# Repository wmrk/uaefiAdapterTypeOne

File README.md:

## License

Licensed under the [CERN Open Hardware Licence Version 2 - Strongly Reciprocal](LICENSE)
(`CERN-OHL-S-2.0`). The text in `LICENSE` is the unmodified canonical licence.

### Additional terms

The following terms are not part of CERN-OHL-S-2.0 and are stated here by the author:

- **#1:** This adapter is intended for off-road land and water vehicles.
- **#2:** This adapter is not compliant with automotive environmental regulations.
- **#3:** This adapter is not approved for manned aircraft applications.

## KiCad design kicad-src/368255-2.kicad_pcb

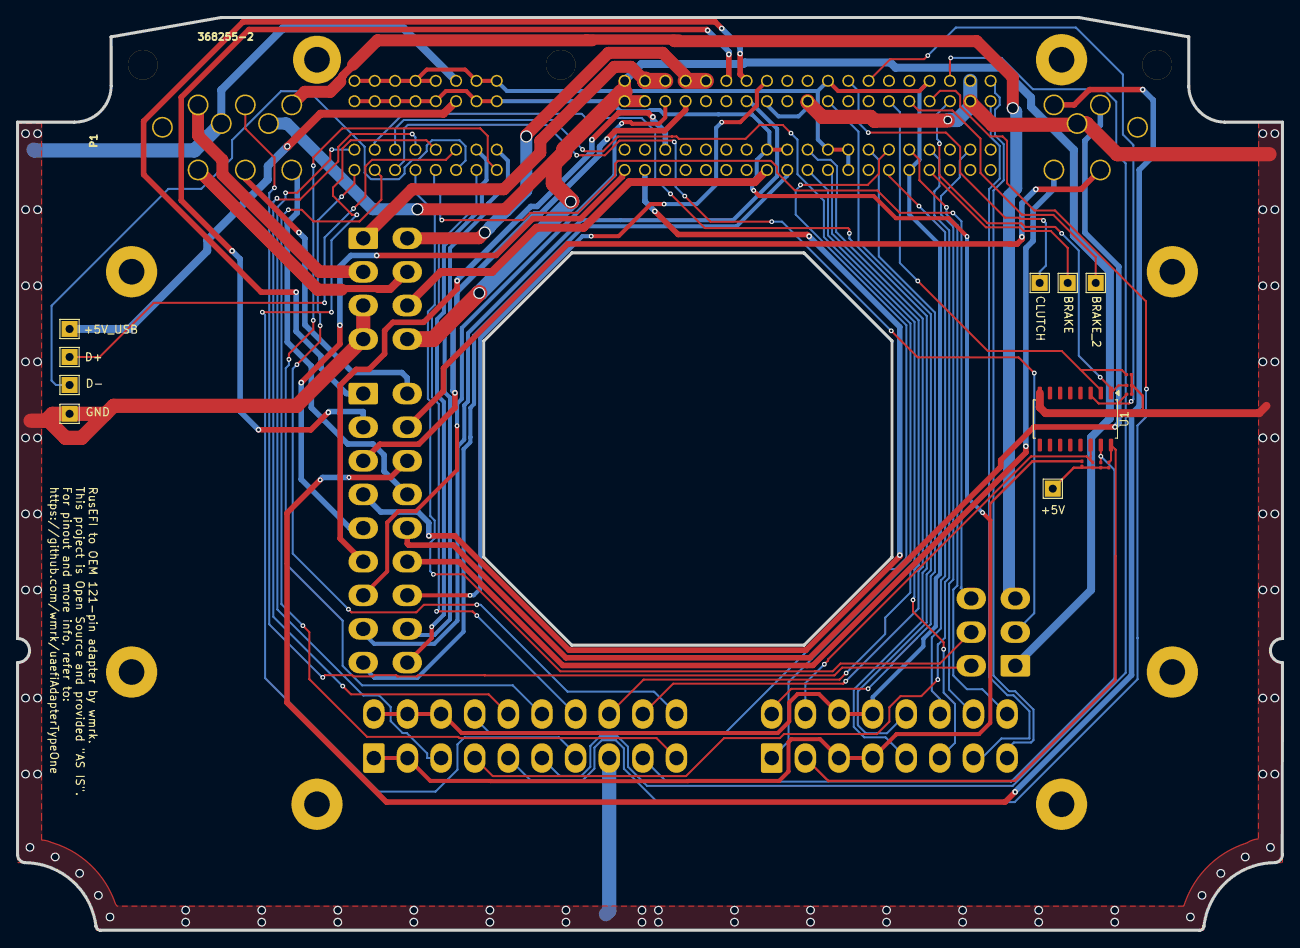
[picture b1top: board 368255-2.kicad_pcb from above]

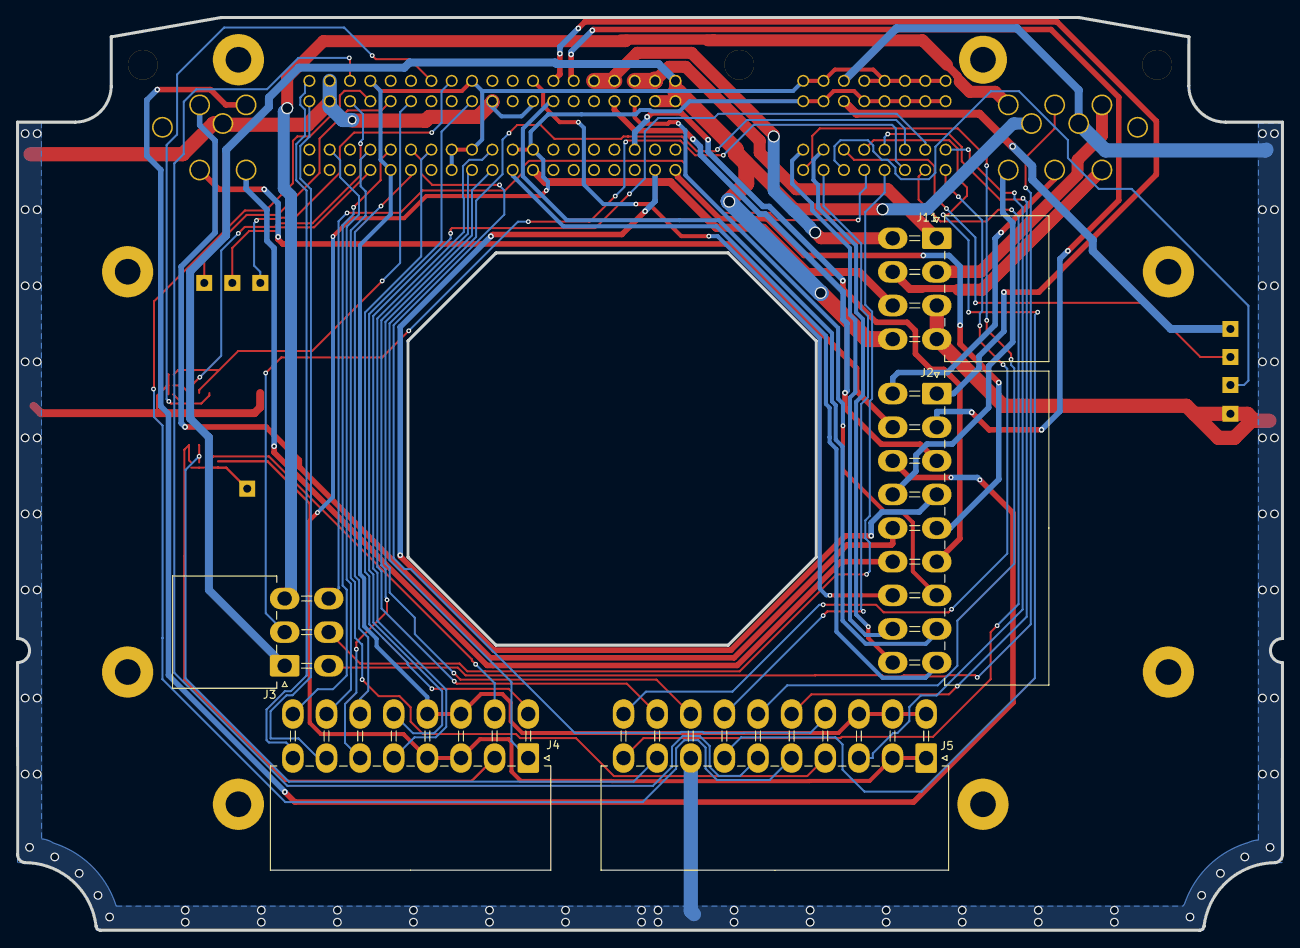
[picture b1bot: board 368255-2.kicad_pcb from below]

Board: 2 copper layers, 158.0 x 114.0 mm, 30 parts (12 on the bottom side), 68 nets.

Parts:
J2: 5569-18A2; Molex_Mini-Fit_Jr_5569-18A2_2x09_P4.20mm_Horizontal
J3: 5569-06A2; Molex_Mini-Fit_Jr_5569-06A2_2x03_P4.20mm_Horizontal
J4: 5569-16A2; Molex_Mini-Fit_Jr_5569-16A2_2x08_P4.20mm_Horizontal
J5: 5569-20A2-new; Molex_Mini-Fit_Jr_5569-20A2_2x10_P4.20mm_Horizontal
J11: 5569-08A2; Molex_Mini-Fit_Jr_5569-08A2_2x04_P4.20mm_Horizontal
J21, J22, J23, J24, J25, J26, J27, J28: Conn_01x01_Pin; TestPoint_THTPad_2.0x2.0mm_Drill1.0mm
P1: 368255-2
R1: R0; R_0201_0603Metric
R2, R3, R4, R8, R9, R10: 10k; R_0201_0603Metric
U1: ULN2003A; SOIC-16_4.55x10.3mm_P1.27mm
hole1: hole1; uaefi_hole
hole2: hole2; uaefi_hole
hole3: hole3; uaefi_hole
hole4: hole4; uaefi_hole
hole5: hole5; uaefi_hole
hole6: hole6; uaefi_hole
hole7: hole7; uaefi_hole
hole8: hole8; uaefi_hole

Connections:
+5VP: J4.3, J4.4, J5.1, J5.2, P1.32, P1.33, P1.90, P1.91, P1.93, P1.94, P1.95, P1.96, P1.97, R1.1
+5VUSB: J24.1 (Pin_1_1), P1.92
+12V: J3.1, J11.8, P1.44, P1.45, P1.63, P1.117
/1_WBO_Ip: J3.5, P1.110
/2_WBO_Vm: J3.6, P1.109
/3_WBO_Heater: J3.3, P1.114
/5_WBO_Rtrim: J3.2, P1.111
/6_WBO_Un: J3.4, P1.115
/12V_KEY_VIGN: J11.7, P1.13
/BRAKE_PEDAL_SENSOR: J22.1 (Pin_1_1), P1.21
/BRAKE_PEDAL_SENSOR_2: J23.1 (Pin_1_1), P1.58
/BUTTON1: P1.60, R10.2, U1.1 (I1)
/BUTTON3: P1.57, R9.2, U1.2 (I2)
/CAN+: J4.7, P1.62
/CAN-: J4.8, P1.81
/CLUTCH_SENSOR: J21.1 (Pin_1_1), P1.74
/CONTITIONER_ON: P1.75, R8.2, U1.3 (I3)
/EGT+: J5.10, P1.112
/EGT-: J5.20, P1.113
/IN_AUX1_EWG_POS_SENSOR: J4.1, P1.103
/IN_AUX2_WBO_ANALOG: J5.3, P1.105
/IN_AUX3_FUEL_PRESSURE_SENSOR: J5.15, P1.102
/IN_BUTTON1: J4.2, R2.2, U1.16 (O1)
/IN_BUTTON2: J4.10, R4.2, U1.14 (O3)
/IN_BUTTON3: J5.9, R3.2, U1.15 (O2)
/IN_CLT: J4.16, P1.39
/IN_FLEX: J4.5, P1.104
/IN_HALL1_SPEED_SENSOR: J5.5, P1.59
/IN_HALL2: J5.6, P1.79
/IN_HALL3: J5.7, P1.101
/IN_IAT: J4.15, P1.42
/IN_KNOCK_RAW: J4.14, P1.19
/IN_MAP: J4.9, P1.37
/IN_PPS1: J4.6, P1.16
/IN_PPS2: J5.4, P1.40
/IN_TPS1: J4.13, P1.54
/IN_TPS2: J5.14, P1.38
/OUT_DC1+: J11.5, P1.66, P1.67
/OUT_DC1-: J11.1, P1.64, P1.65
/OUT_DC2+: J11.6, P1.121
/OUT_DC2-: J11.2, P1.116
/OUT_IGN1: J2.15, P1.5
/OUT_IGN2: J2.14, P1.1
/OUT_IGN3: J2.12, P1.2
/OUT_IGN4: J2.11, P1.4
/OUT_IGN5: J2.13, P1.119
/OUT_IGN6: J2.10, P1.120
/OUT_INJ1: J2.6, P1.27
/OUT_INJ2: J2.5, P1.6
/OUT_INJ3: J2.4, P1.7
/OUT_INJ4: J2.3, P1.47
/OUT_INJ5: J2.2, P1.68
/OUT_INJ6: J2.1, P1.69
/OUT_LS1: J2.7, P1.46
/OUT_LS2: J2.18, P1.99
/OUT_LS3: J2.17, P1.98
/OUT_LS4: J2.16, P1.70
/OUT_LS_HOT1: J2.9, P1.14
/OUT_LS_HOT2: J2.8, P1.50
/USB_D+: J26.1 (Pin_1_1), P1.100
/USB_D-: J27.1 (Pin_1_1), P1.108
/VR_DISCRETE+: J5.18, P1.15
/VR_DISCRETE-: J5.19, P1.34
/VR_MAX9924+: J5.16, P1.106
/VR_MAX9924-: J5.17, P1.107
GND: J5.8, J11.3, J11.4, J28.1 (Pin_1_1), P1.3, P1.51, P1.53, P1.61, P1.80, P1.84, P1.118, R8.1, R9.1, R10.1, U1.8 (GND)
GNDA: J4.11, J4.12, J5.11, J5.12, J5.13, P1.17, P1.20, P1.35, P1.36, P1.73, P1.78, P1.82, P1.83, P1.85, P1.86, P1.87, P1.88, P1.89
unnamed: J25.1 (Pin_1_1), R1.2, R2.1, R3.1, R4.1
